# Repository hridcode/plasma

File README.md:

# Plasma

Plasma is an ortholinear staggered split keyboard that connects with BLE. It has an OLED display and rotary encoder as well for extra fun! With 6 columns and 5 rows, plus space keys right at the thumbs, what's not to love?

# Pictures

|Schematic (L)|Schematic (R)|PCB|Case|
|---|---|---|---|
|||||

# BOM

|Item|Quantity|Cost|Source|
|---|---|---|---|
|Seeed Studio XIAO nRF52840 Plus|2|20.80|https://www.seeedstudio.com/Seeed-Studio-XIAO-nRF52840-Plus-p-6359.html|
|Key switches|1|17.34|https://www.aliexpress.us/item/3256810602342636.html?spm=a2g0o.cart.0.0.ac9b38da2CRcQI&mp=1&pdp_npi=6%40dis%21USD%21USD+37.16%21USD+17.34%21%21USD+17.34%21%21%21%402101ef5e17799000531104284e6748%2112000053510026411%21ct%21US%216217402649%21%211%210%21&gatewayAdapt=glo2usa|
YMDK ZDA black keycaps|1|16.94|https://www.aliexpress.us/item/3256808606272435.html?spm=a2g0o.productlist.main.2.559368afxvvDRE&algo_pvid=be438f86-bbf9-41a8-9036-e1f76fb050b9&algo_exp_id=be438f86-bbf9-41a8-9036-e1f76fb050b9-1&pdp_ext_f=%7B%22order%22%3A%22360%22%2C%22eval%22%3A%221%22%2C%22fromPage%22%3A%22search%22%7D&pdp_npi=6%40dis%21USD%2125.64%2116.94%21%21%2125.64%2116.94%21%402101eee917777475325795902ef308%2112000046680586806%21sea%21US%210%21ABX%211%210%21n_tag%3A-29910%3Bd%3A7e394ebc%3Bm03_new_user%3A-29895%3BpisId%3A5000000203537380&curPageLogUid=46jL7OyEjN3m&utparam-url=scene%3Asearch%7Cquery_from%3A%7Cx_object_id%3A1005008792587187%7C_p_origin_prod%3A|
|EC11 rotary encoders|1|3.08|https://www.aliexpress.us/item/3256807457610925.html?spm=a2g0o.productlist.main.11.1a7a3a52762UqH&algo_pvid=92408ecb-c68b-4c06-bbd7-933c560c669f&algo_exp_id=92408ecb-c68b-4c06-bbd7-933c560c669f-10&pdp_ext_f=%7B%22order%22%3A%22306%22%2C%22eval%22%3A%221%22%2C%22fromPage%22%3A%22search%22%7D&pdp_npi=6%40dis%21USD%213.05%210.99%21%21%213.05%210.99%21%402103128817777477285447626eb976%2112000041629865923%21sea%21US%210%21ABX%211%210%21n_tag%3A-29910%3Bd%3A7e394ebc%3Bm03_new_user%3A-29895%3BpisId%3A5000000203537378&curPageLogUid=Gnz1vOJZ5LKS&utparam-url=scene%3Asearch%7Cquery_from%3A%7Cx_object_id%3A1005007643925677%7C_p_origin_prod%3A|
|SSD1306 OLED displays|1|3.50|https://www.aliexpress.us/item/3256806882812437.html?spm=a2g0o.productlist.main.12.eaf7xkmuxkmuyu&aem_p4p_detail=202605021150319941447284803840003421400&algo_pvid=a7d109fa-8753-49ed-9ee5-6269bcef89e7&algo_exp_id=a7d109fa-8753-49ed-9ee5-6269bcef89e7-11&pdp_ext_f=%7B%22order%22%3A%22231%22%2C%22eval%22%3A%221%22%2C%22fromPage%22%3A%22search%22%7D&pdp_npi=6%40dis%21USD%213.50%210.99%21%21%2123.76%216.71%21%40210328d417777478315891457e3f77%2112000039302444378%21sea%21US%210%21ABX%211%210%21n_tag%3A-29910%3Bd%3A7e394ebc%3Bm03_new_user%3A-29895%3BpisId%3A5000000203537378&curPageLogUid=kfCFOX5XGs2T&utparam-url=scene%3Asearch%7Cquery_from%3A%7Cx_object_id%3A1005007069127189%7C_p_origin_prod%3A&search_p4p_id=202605021150319941447284803840003421400_3|
|LiPo batteries|1|5.02|https://www.aliexpress.us/item/3256811857707355.html?spm=a2g0o.productlist.seoads.3.456b4Og94Og9yr&p4p_pvid=202605021152471438651116653440005803865_2&_gl=1*1o3g1tt*_gcl_au*OTA5OTMxNDQ1LjE3NzczMzkxNjI.*_ga*MTcxNjY4NTYwMzQxODUuMTc3NzMzOTE1OTMzOQ..*_ga_VED1YSGNC7*czE3Nzc3NDcxOTckbzQkZzEkdDE3Nzc3NDc5NjgkajQ2JGwwJGgw&gatewayAdapt=glo2usa4itemAdapt|
|JST connectors|1|2.79|https://www.aliexpress.us/item/3256801462843682.html?spm=a2g0o.productlist.main.2.4d363896a8Ljc7&algo_pvid=d87fb88e-cb9d-45e2-af7d-d1767d5bd963&algo_exp_id=d87fb88e-cb9d-45e2-af7d-d1767d5bd963-1&pdp_ext_f=%7B%22order%22%3A%2217874%22%2C%22eval%22%3A%221%22%2C%22fromPage%22%3A%22search%22%7D&pdp_npi=6%40dis%21USD%212.07%210.99%21%21%212.07%210.99%21%402101e80317777480847362566e5f5f%2112000016976908168%21sea%21US%216217402649%21ACX%211%210%21n_tag%3A-29919%3Bd%3A7e394ebc%3Bm03_new_user%3A-29894%3BpisId%3A5000000203531336&curPageLogUid=LgkQ6isYab0G&utparam-url=scene%3Asearch%7Cquery_from%3A%7Cx_object_id%3A1005001649158434%7C_p_origin_prod%3A|
|M3 inserts|1|0.73|https://www.aliexpress.com/ssr/300000512/BundleDeals2?spm=a2g0o.productlist.main.19.5741GIIvGIIvOR&productIds=1005006967339727%3A12000038886016094&pha_manifest=ssr&_immersiveMode=true&disableNav=YES&sourceName=SEARCHProduct&utparam-url=scene%3Asearch%7Cquery_from%3A%7Cx_object_id%3A1005006967339727%7C_p_origin_prod%3A1005006472702418&pvid=82723a9f-b0cf-48ed-baea-33ebdaed60dd&_gl=1*1pt504n*_gcl_au*OTA5OTMxNDQ1LjE3NzczMzkxNjI.*_ga*MTcxNjY4NTYwMzQxODUuMTc3NzMzOTE1OTMzOQ..*_ga_VED1YSGNC7*czE3Nzc3NDcxOTckbzQkZzEkdDE3Nzc3NDgxODUkajI5JGwwJGgw|
|M3x16 screws|1|2.92|https://www.aliexpress.us/item/3256808523663879.html?spm=a2g0o.productlist.main.8.1d9748abUOXQOY&aem_p4p_detail=202605021157454379770303191570003438720&algo_pvid=7d6700f1-e58f-480a-beca-dca4aa50249d&algo_exp_id=7d6700f1-e58f-480a-beca-dca4aa50249d-7&pdp_ext_f=%7B%22order%22%3A%2210955%22%2C%22eval%22%3A%221%22%2C%22fromPage%22%3A%22search%22%7D&pdp_npi=6%40dis%21USD%211.65%210.99%21%21%2111.22%216.70%21%402101c59117777482655617764e6a55%2112000046342342830%21sea%21US%216217402649%21ACX%211%210%21n_tag%3A-29919%3Bd%3A7e394ebc%3Bm03_new_user%3A-29894%3BpisId%3A5000000203531336&curPageLogUid=TUfYajctXH1A&utparam-url=scene%3Asearch%7Cquery_from%3A%7Cx_object_id%3A1005008709978631%7C_p_origin_prod%3A&search_p4p_id=202605021157454379770303191570003438720_2|
|M3x6 screws|1|2.14|https://www.aliexpress.us/item/3256808523663879.html?spm=a2g0o.productlist.main.8.1d9748abUOXQOY&aem_p4p_detail=202605021157454379770303191570003438720&algo_pvid=7d6700f1-e58f-480a-beca-dca4aa50249d&algo_exp_id=7d6700f1-e58f-480a-beca-dca4aa50249d-7&pdp_ext_f=%7B%22order%22%3A%2210955%22%2C%22eval%22%3A%221%22%2C%22fromPage%22%3A%22search%22%7D&pdp_npi=6%40dis%21USD%211.65%210.99%21%21%2111.22%216.70%21%402101c59117777482655617764e6a55%2112000046342342830%21sea%21US%216217402649%21ACX%211%210%21n_tag%3A-29919%3Bd%3A7e394ebc%3Bm03_new_user%3A-29894%3BpisId%3A5000000203531336&curPageLogUid=TUfYajctXH1A&utparam-url=scene%3Asearch%7Cquery_from%3A%7Cx_object_id%3A1005008709978631%7C_p_origin_prod%3A&search_p4p_id=202605021157454379770303191570003438720_2|
|Hotswap sockets|1|3.89|https://www.aliexpress.com/ssr/300000512/BundleDeals2?spm=a2g0o.productlist.main.1.5576445aH5UPRN&productIds=1005007052649640%3A12000039244942221&pha_manifest=ssr&_immersiveMode=true&disableNav=YES&sourceName=SEARCHProduct&utparam-url=scene%3Asearch%7Cquery_from%3A%7Cx_object_id%3A1005007052649640%7C_p_origin_prod%3A&pvid=a869fe91-1e83-49f5-a60f-e5c6ccd18303&_gl=1*1hwpay8*_gcl_au*OTA5OTMxNDQ1LjE3NzczMzkxNjI.*_ga*MTcxNjY4NTYwMzQxODUuMTc3NzMzOTE1OTMzOQ..*_ga_VED1YSGNC7*czE3Nzc3NDcxOTckbzQkZzEkdDE3Nzc3NDgzNjYkajQ3JGwwJGgw
|PCBs|1|15.20|https://cart.jlcpcb.com/quote?stencilLayer=2&stencilWidth=253&stencilLength=110&stencilCounts=5&plateType=1&spm=Jlcpcb.Homepage.1010|
|0805 resistors|1|6.50|https://www.aliexpress.us/item/3256805806582589.html?spm=a2g0o.productlist.main.4.201a6bb21ZnQ3n&aem_p4p_detail=2026050213364611852948673684600003349288&algo_pvid=14aaef76-7e01-40f9-8270-f42b60f5a41f&algo_exp_id=14aaef76-7e01-40f9-8270-f42b60f5a41f-3&pdp_ext_f=%7B%22order%22%3A%22387%22%2C%22eval%22%3A%221%22%2C%22fromPage%22%3A%22search%22%7D&pdp_npi=6%40dis%21USD%215.97%213.97%21%21%2140.58%2126.99%21%402103128917777542067105272eb9d2%2112000035234708072%21sea%21US%216217402649%21ACX%211%210%21n_tag%3A-29919%3Bd%3A7e394ebc%3Bm03_new_user%3A-29894%3BpisId%3A5000000204885259&curPageLogUid=6eeBEBX80vKN&utparam-url=scene%3Asearch%7Cquery_from%3A%7Cx_object_id%3A1005005992897341%7C_p_origin_prod%3A&search_p4p_id=2026050213364611852948673684600003349288_1|
|3D printed case (from Printing Legion)|1|6.00|

Total: $120.17

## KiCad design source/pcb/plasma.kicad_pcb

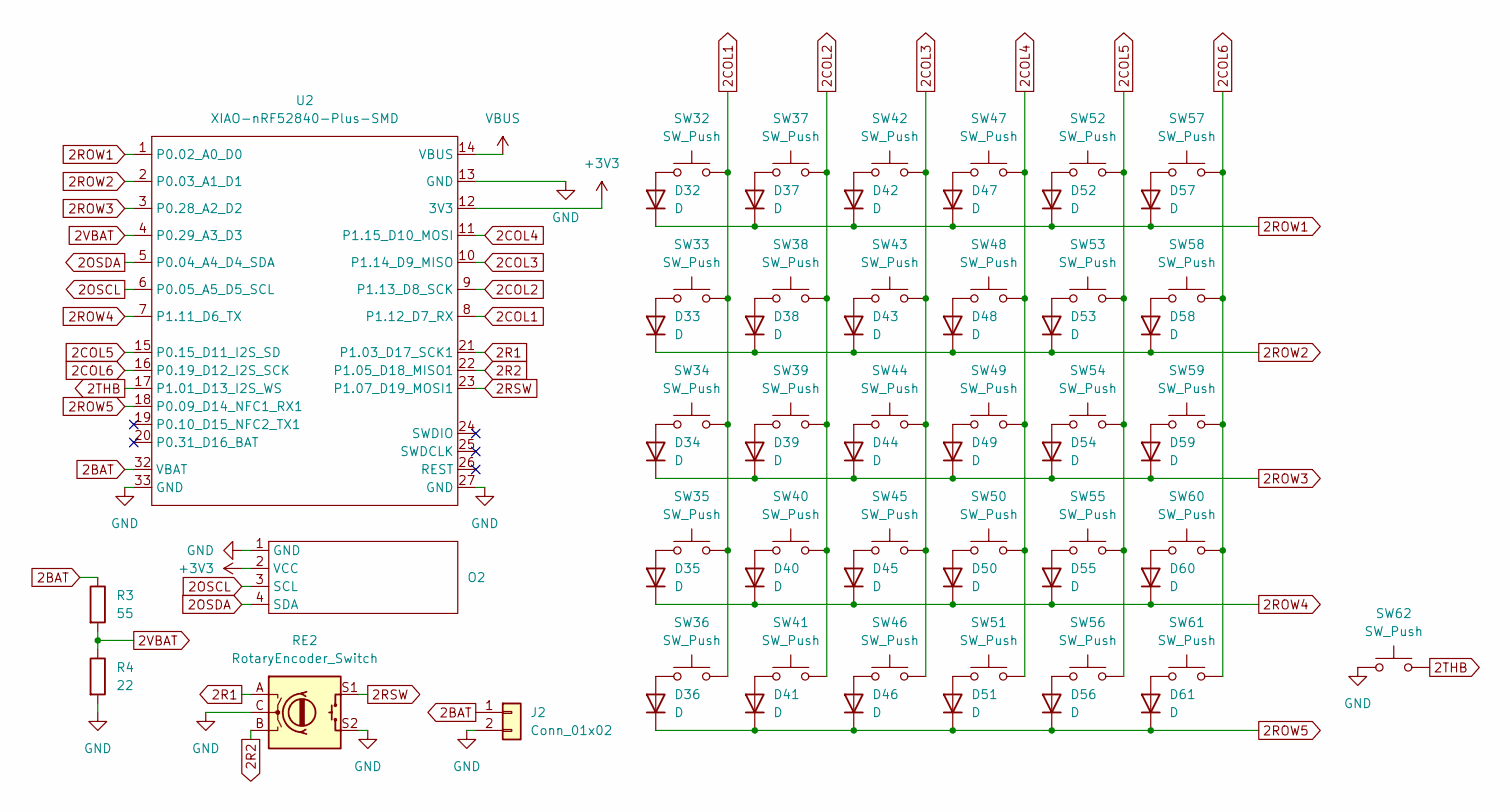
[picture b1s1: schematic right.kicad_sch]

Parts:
D32, D33, D34, D35, D36, D37, D38, D39, D40, D41, D42, D43, D44, D45, D46, D47, D48, D49, D50, D51, D52, D53, D54, D55, D56, D57, D58, D59, D60, D61: D; D_0805_2012Metric_Pad1.15x1.40mm_HandSolder
J2: Conn_01x02; JST_EH_B2B-EH-A_1x02_P2.50mm_Vertical
O2: SSD1306-4pin-0.91
R3: 55; R_0805_2012Metric_Pad1.20x1.40mm_HandSolder
R4: 22; R_0805_2012Metric_Pad1.20x1.40mm_HandSolder
RE2: RotaryEncoder_Switch; RotaryEncoder_Alps_EC11E-Switch_Vertical_H20mm_MountingHoles
SW32, SW33, SW34, SW35, SW36, SW37, SW38, SW39, SW40, SW41, SW42, SW43, SW44, SW45, SW46, SW47, SW48, SW49, SW50, SW51, SW52, SW53, SW54, SW55, SW56, SW57, SW58, SW59, SW60, SW61, SW62: SW_Push; SW_MX_HotSwap_THT
U2: XIAO-nRF52840-Plus-SMD

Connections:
2BAT: J2.1, R3.1, U2.32 (VBAT)
2COL1: SW32.2, SW33.2, SW34.2, SW35.2, SW36.2, U2.8 (P1.12_D7_RX)
2COL2: SW37.2, SW38.2, SW39.2, SW40.2, SW41.2, U2.9 (P1.13_D8_SCK)
2COL3: SW42.2, SW43.2, SW44.2, SW45.2, SW46.2, U2.10 (P1.14_D9_MISO)
2COL4: SW47.2, SW48.2, SW49.2, SW50.2, SW51.2, U2.11 (P1.15_D10_MOSI)
2COL5: SW52.2, SW53.2, SW54.2, SW55.2, SW56.2, U2.15 (P0.15_D11_I2S_SD)
2COL6: SW57.2, SW58.2, SW59.2, SW60.2, SW61.2, U2.16 (P0.19_D12_I2S_SCK)
2OSCL: O2.3 (SCL), U2.6 (P0.05_A5_D5_SCL)
2OSDA: O2.4 (SDA), U2.5 (P0.04_A4_D4_SDA)
2R1: RE2.A, U2.21 (P1.03_D17_SCK1)
2R2: RE2.B, U2.22 (P1.05_D18_MISO1)
2ROW1: D32.1 (K), D37.1 (K), D42.1 (K), D47.1 (K), D52.1 (K), D57.1 (K), U2.1 (P0.02_A0_D0)
2ROW2: D33.1 (K), D38.1 (K), D43.1 (K), D48.1 (K), D53.1 (K), D58.1 (K), U2.2 (P0.03_A1_D1)
2ROW3: D34.1 (K), D39.1 (K), D44.1 (K), D49.1 (K), D54.1 (K), D59.1 (K), U2.3 (P0.28_A2_D2)
2ROW4: D35.1 (K), D40.1 (K), D45.1 (K), D50.1 (K), D55.1 (K), D60.1 (K), U2.7 (P1.11_D6_TX)
2ROW5: D36.1 (K), D41.1 (K), D46.1 (K), D51.1 (K), D56.1 (K), D61.1 (K), U2.18 (P0.09_D14_NFC1_RX1)
2RSW: RE2.S1, U2.23 (P1.07_D19_MOSI1)
2THB: SW62.2, U2.17 (P1.01_D13_I2S_WS)
2VBAT: R3.2, R4.1, U2.4 (P0.29_A3_D3)
+3V3: O2.2 (VCC), U2.12 (3V3); also elsewhere on the board
GND: J2.2, O2.1 (GND), R4.2, RE2.C, RE2.S2, SW62.1, U2.13 (GND), U2.27 (GND), U2.33 (GND); also elsewhere on the board
unnamed: D32.2 (A), SW32.1
unnamed: D33.2 (A), SW33.1
unnamed: D34.2 (A), SW34.1
unnamed: D35.2 (A), SW35.1
unnamed: D36.2 (A), SW36.1
unnamed: D37.2 (A), SW37.1
unnamed: D38.2 (A), SW38.1
unnamed: D39.2 (A), SW39.1
unnamed: D40.2 (A), SW40.1
unnamed: D41.2 (A), SW41.1
unnamed: D42.2 (A), SW42.1
unnamed: D43.2 (A), SW43.1
unnamed: D44.2 (A), SW44.1
unnamed: D45.2 (A), SW45.1
unnamed: D46.2 (A), SW46.1
unnamed: D47.2 (A), SW47.1
unnamed: D48.2 (A), SW48.1
unnamed: D49.2 (A), SW49.1
unnamed: D50.2 (A), SW50.1
unnamed: D51.2 (A), SW51.1
unnamed: D52.2 (A), SW52.1
unnamed: D53.2 (A), SW53.1
unnamed: D54.2 (A), SW54.1
unnamed: D55.2 (A), SW55.1
unnamed: D56.2 (A), SW56.1
unnamed: D57.2 (A), SW57.1
unnamed: D58.2 (A), SW58.1
unnamed: D59.2 (A), SW59.1
unnamed: D60.2 (A), SW60.1
unnamed: D61.2 (A), SW61.1
VBUS: U2.14 (VBUS); also elsewhere on the board

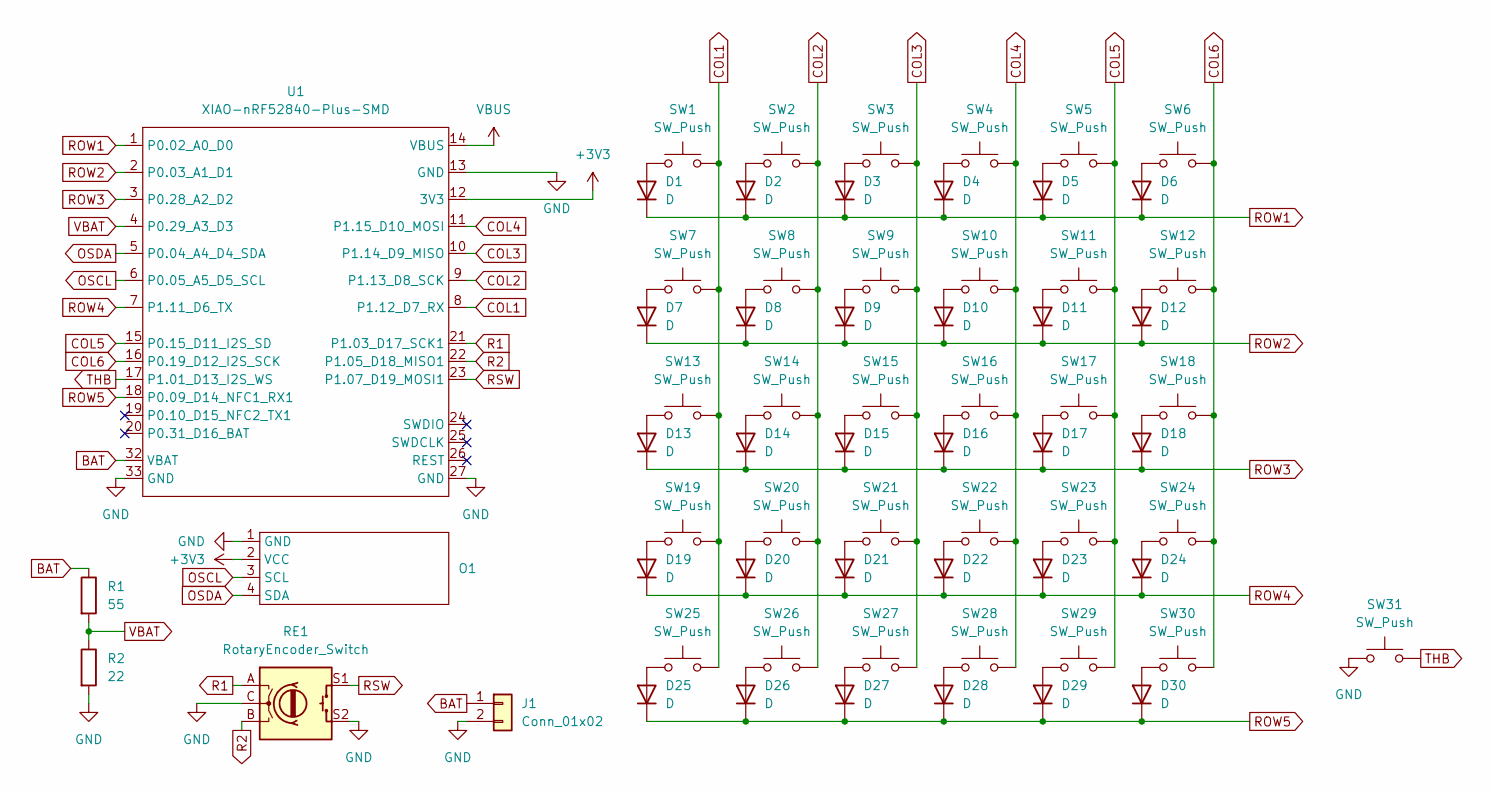
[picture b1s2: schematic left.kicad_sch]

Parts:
D1, D2, D3, D4, D5, D6, D7, D8, D9, D10, D11, D12, D13, D14, D15, D16, D17, D18, D19, D20, D21, D22, D23, D24, D25, D26, D27, D28, D29, D30: D; D_0805_2012Metric_Pad1.15x1.40mm_HandSolder
J1: Conn_01x02; JST_EH_B2B-EH-A_1x02_P2.50mm_Vertical
O1: SSD1306-4pin-0.91
R1: 55; R_0805_2012Metric_Pad1.20x1.40mm_HandSolder
R2: 22; R_0805_2012Metric_Pad1.20x1.40mm_HandSolder
RE1: RotaryEncoder_Switch; RotaryEncoder_Alps_EC11E-Switch_Vertical_H20mm_MountingHoles
SW1, SW2, SW3, SW4, SW5, SW6, SW7, SW8, SW9, SW10, SW11, SW12, SW13, SW14, SW15, SW16, SW17, SW18, SW19, SW20, SW21, SW22, SW23, SW24, SW25, SW26, SW27, SW28, SW29, SW30, SW31: SW_Push; SW_MX_HotSwap_THT
U1: XIAO-nRF52840-Plus-SMD

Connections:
+3V3: O1.2 (VCC), U1.12 (3V3); also elsewhere on the board
BAT: J1.1, R1.1, U1.32 (VBAT)
COL1: SW1.2, SW7.2, SW13.2, SW19.2, SW25.2, U1.8 (P1.12_D7_RX)
COL2: SW2.2, SW8.2, SW14.2, SW20.2, SW26.2, U1.9 (P1.13_D8_SCK)
COL3: SW3.2, SW9.2, SW15.2, SW21.2, SW27.2, U1.10 (P1.14_D9_MISO)
COL4: SW4.2, SW10.2, SW16.2, SW22.2, SW28.2, U1.11 (P1.15_D10_MOSI)
COL5: SW5.2, SW11.2, SW17.2, SW23.2, SW29.2, U1.15 (P0.15_D11_I2S_SD)
COL6: SW6.2, SW12.2, SW18.2, SW24.2, SW30.2, U1.16 (P0.19_D12_I2S_SCK)
GND: J1.2, O1.1 (GND), R2.2, RE1.C, RE1.S2, SW31.1, U1.13 (GND), U1.27 (GND), U1.33 (GND); also elsewhere on the board
unnamed: D1.2 (A), SW1.1
unnamed: D2.2 (A), SW2.1
unnamed: D3.2 (A), SW3.1
unnamed: D4.2 (A), SW4.1
unnamed: D5.2 (A), SW5.1
unnamed: D6.2 (A), SW6.1
unnamed: D7.2 (A), SW7.1
unnamed: D8.2 (A), SW8.1
unnamed: D9.2 (A), SW9.1
unnamed: D10.2 (A), SW10.1
unnamed: D11.2 (A), SW11.1
unnamed: D12.2 (A), SW12.1
unnamed: D13.2 (A), SW13.1
unnamed: D14.2 (A), SW14.1
unnamed: D15.2 (A), SW15.1
unnamed: D16.2 (A), SW16.1
unnamed: D17.2 (A), SW17.1
unnamed: D18.2 (A), SW18.1
unnamed: D19.2 (A), SW19.1
unnamed: D20.2 (A), SW20.1
unnamed: D21.2 (A), SW21.1
unnamed: D22.2 (A), SW22.1
unnamed: D23.2 (A), SW23.1
unnamed: D24.2 (A), SW24.1
unnamed: D25.2 (A), SW25.1
unnamed: D26.2 (A), SW26.1
unnamed: D27.2 (A), SW27.1
unnamed: D28.2 (A), SW28.1
unnamed: D29.2 (A), SW29.1
unnamed: D30.2 (A), SW30.1
OSCL: O1.3 (SCL), U1.6 (P0.05_A5_D5_SCL)
OSDA: O1.4 (SDA), U1.5 (P0.04_A4_D4_SDA)
R1: RE1.A, U1.21 (P1.03_D17_SCK1)
R2: RE1.B, U1.22 (P1.05_D18_MISO1)
ROW1: D1.1 (K), D2.1 (K), D3.1 (K), D4.1 (K), D5.1 (K), D6.1 (K), U1.1 (P0.02_A0_D0)
ROW2: D7.1 (K), D8.1 (K), D9.1 (K), D10.1 (K), D11.1 (K), D12.1 (K), U1.2 (P0.03_A1_D1)
ROW3: D13.1 (K), D14.1 (K), D15.1 (K), D16.1 (K), D17.1 (K), D18.1 (K), U1.3 (P0.28_A2_D2)
ROW4: D19.1 (K), D20.1 (K), D21.1 (K), D22.1 (K), D23.1 (K), D24.1 (K), U1.7 (P1.11_D6_TX)
ROW5: D25.1 (K), D26.1 (K), D27.1 (K), D28.1 (K), D29.1 (K), D30.1 (K), U1.18 (P0.09_D14_NFC1_RX1)
RSW: RE1.S1, U1.23 (P1.07_D19_MOSI1)
THB: SW31.2, U1.17 (P1.01_D13_I2S_WS)
VBAT: R1.2, R2.1, U1.4 (P0.29_A3_D3)
VBUS: U1.14 (VBUS); also elsewhere on the board

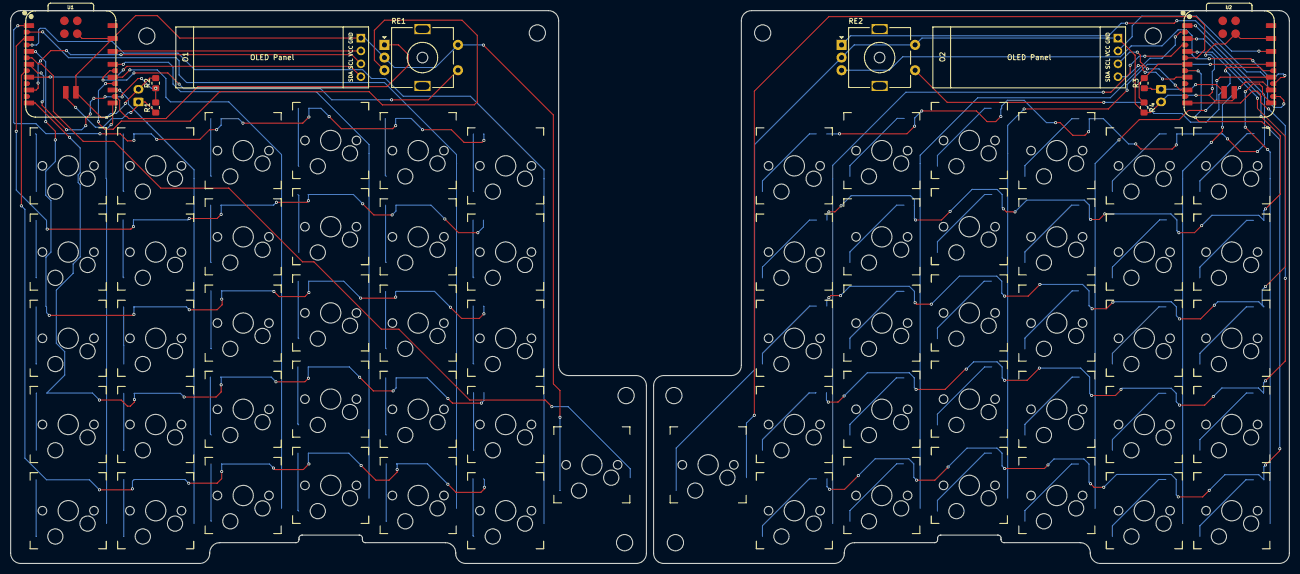
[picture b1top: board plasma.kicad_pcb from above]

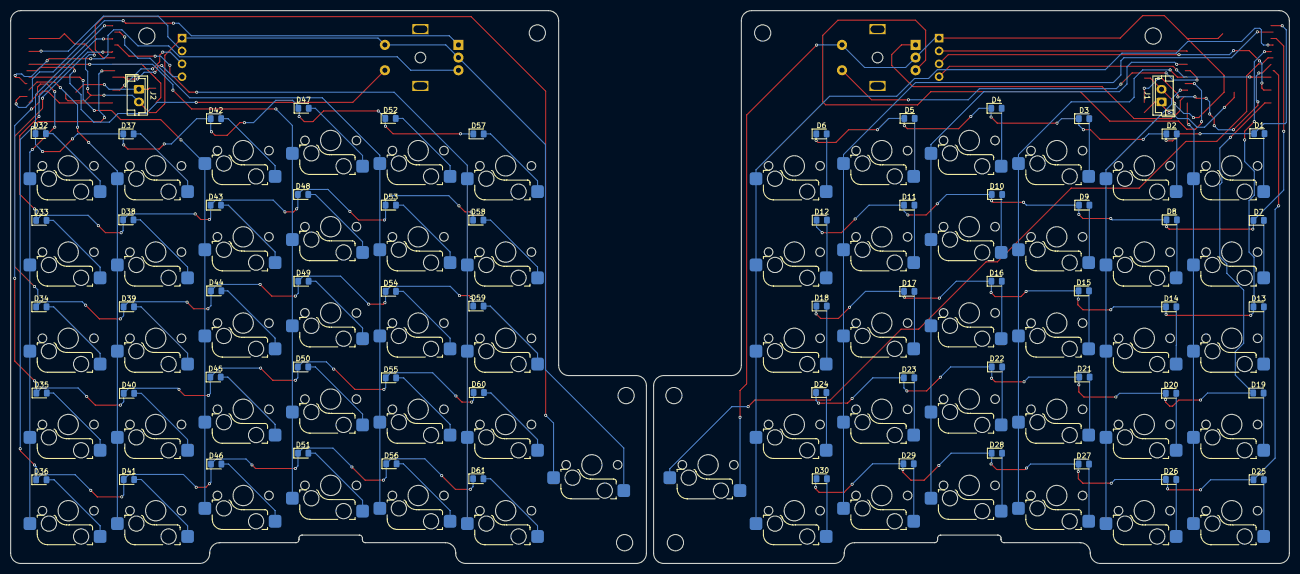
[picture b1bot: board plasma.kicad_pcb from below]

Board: 2 copper layers, 252.1 x 109.0 mm, 134 parts (62 on the bottom side), 101 nets.

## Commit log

2026-05-02 Added production, source, BOM, and README.md
2026-05-02 Updated BOM
